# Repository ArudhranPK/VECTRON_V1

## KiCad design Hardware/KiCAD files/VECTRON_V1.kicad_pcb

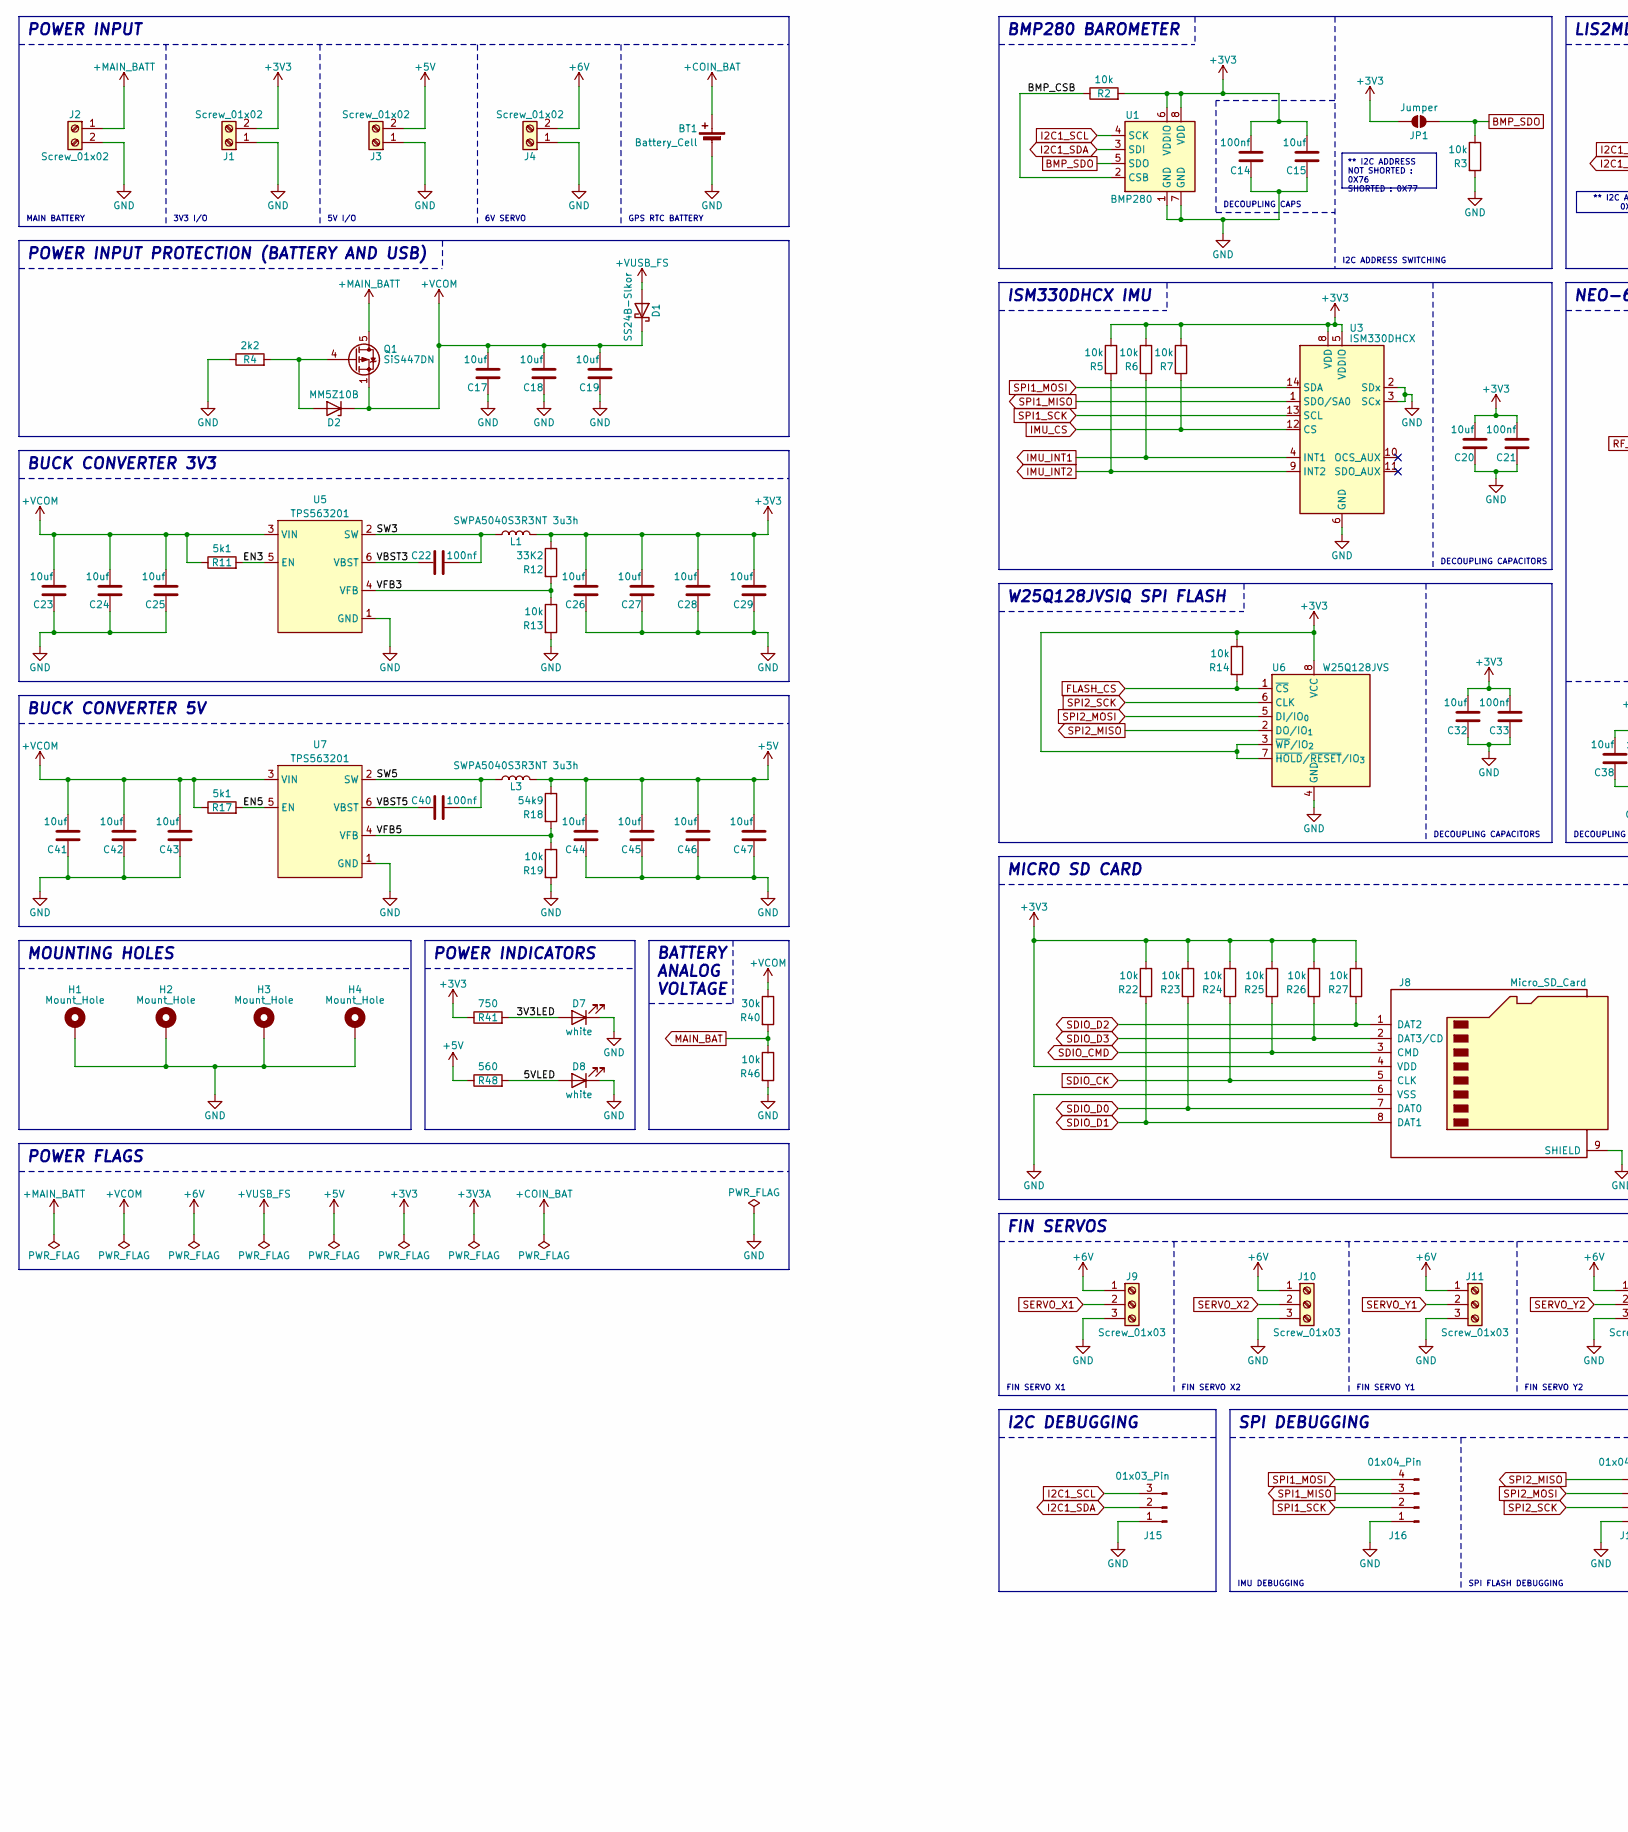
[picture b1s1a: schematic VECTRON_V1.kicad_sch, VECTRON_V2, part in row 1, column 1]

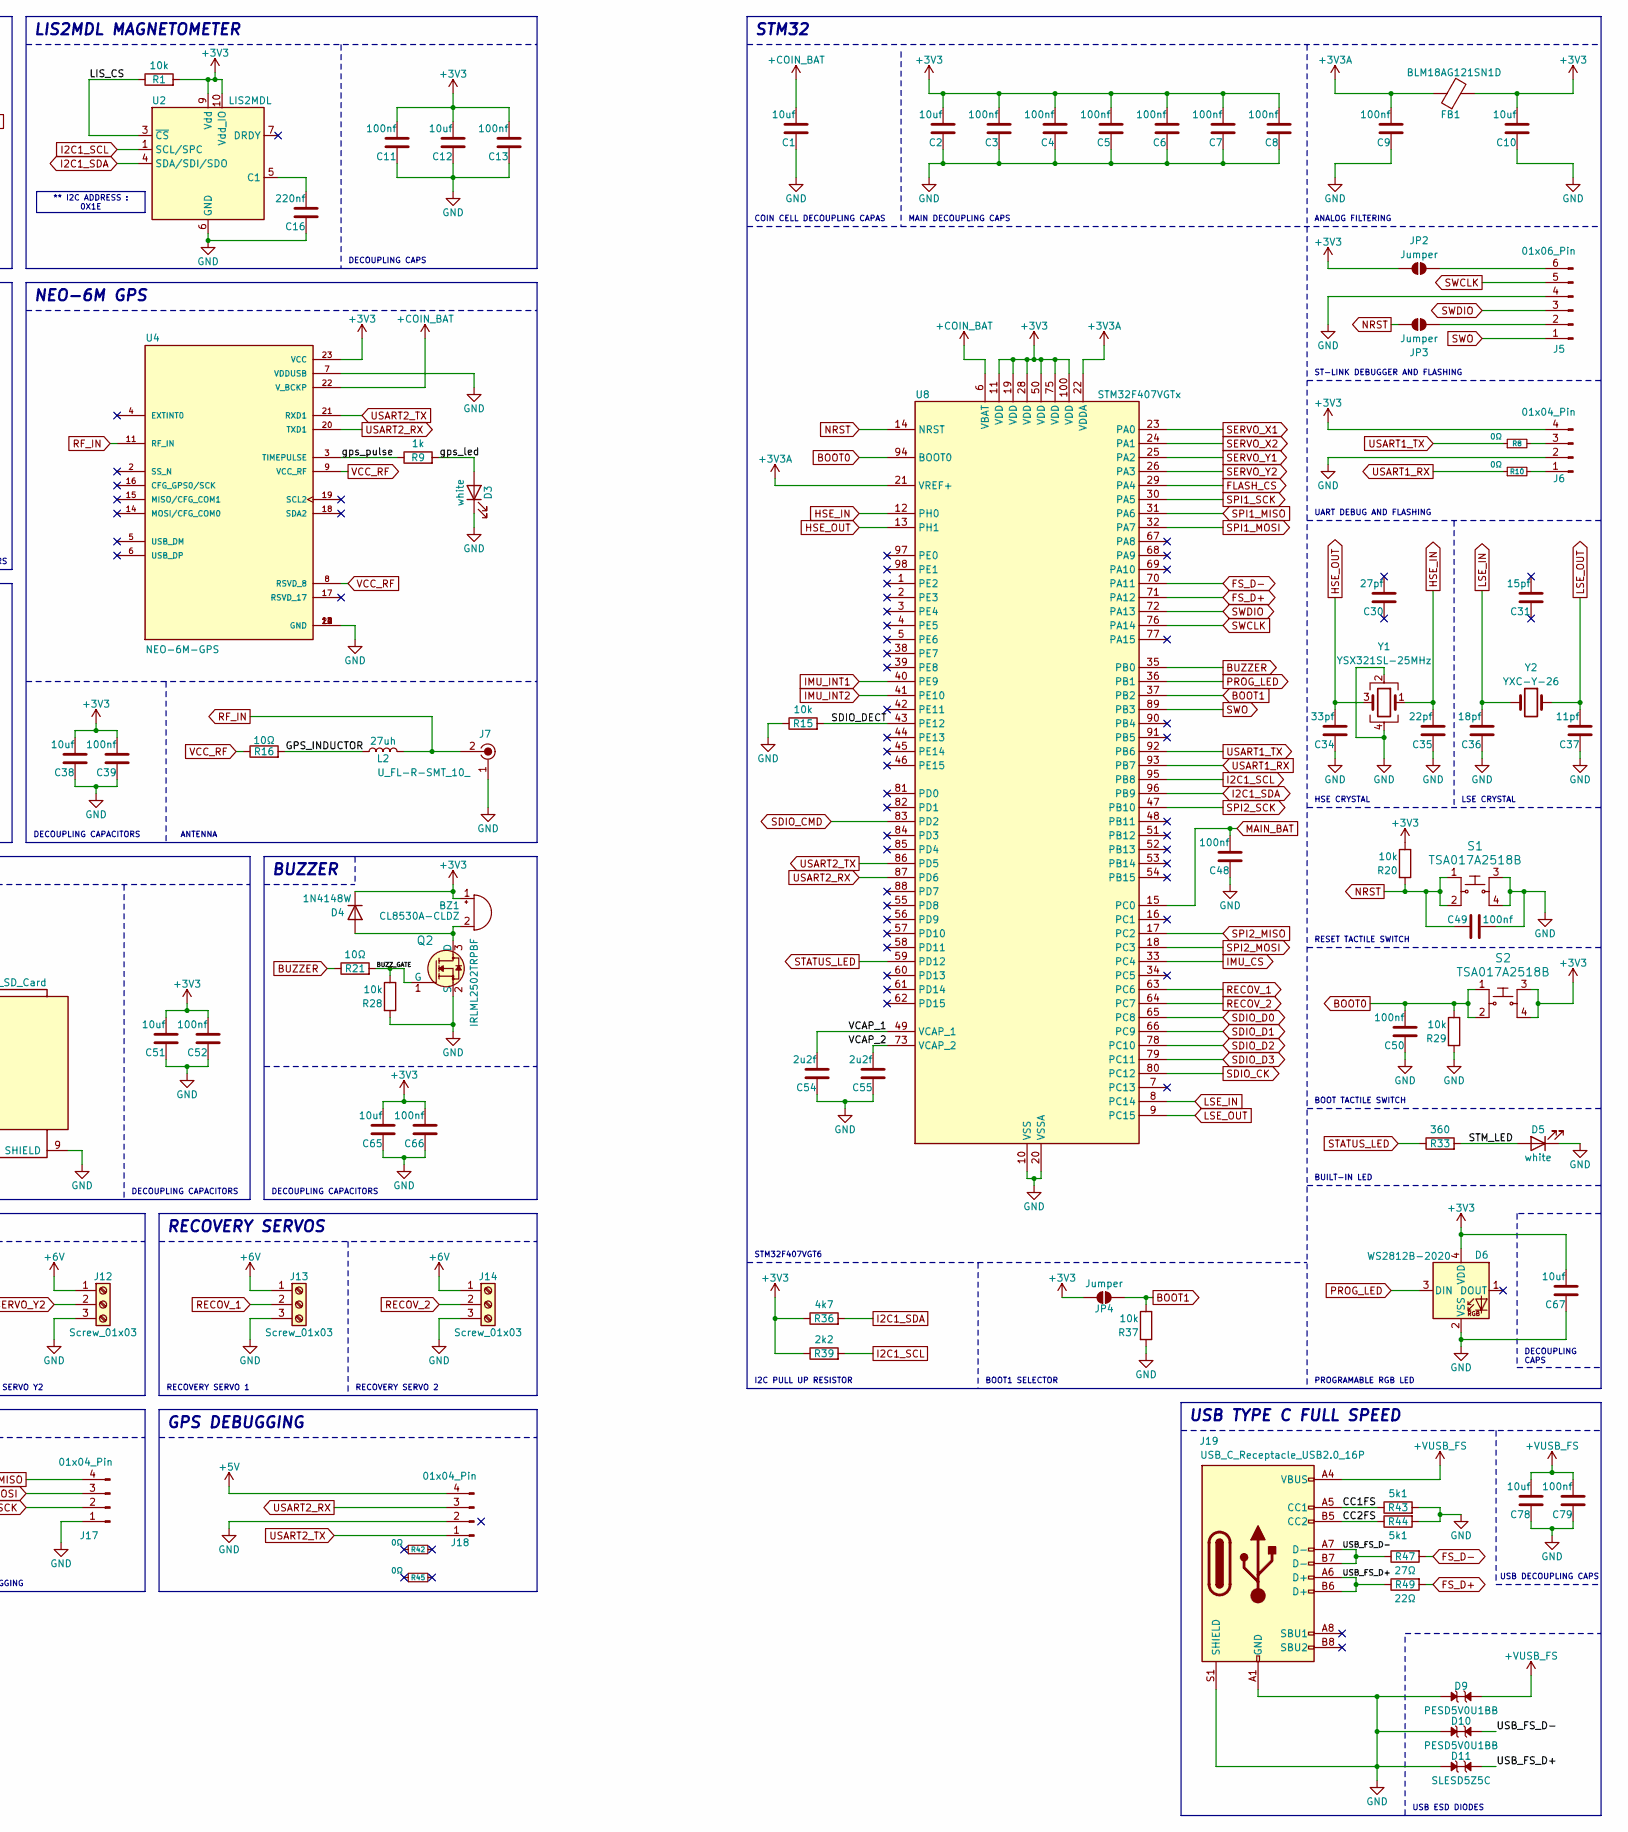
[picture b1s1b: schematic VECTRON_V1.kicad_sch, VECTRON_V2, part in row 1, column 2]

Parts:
BT1: Battery_Cell; BatteryHolder_Multicomp_BC-2001_1x2032_1
BZ1: CL8530A-CLDZ; MagneticBuzzer_CUI_CMT-8504-100-SMT
C1, C2, C10, C12, C15, C17, C18, C19, C20, C23, C24, C25, C26, C27, C28, C29, C32, C38, C41, C42, C43, C44, C45, C46, C47, C51, C65, C67, C78: 10uf; C_0603_1608Metric
C3, C4, C5, C6, C7, C8, C9, C11, C13, C14, C21, C22, C33, C39, C40, C48, C49, C50, C52, C66, C79: 100nf; C_0603_1608Metric
C16: 220nf; C_0603_1608Metric
C30: 27pf; C_0402_1005Metric
C31: 15pf; C_0402_1005Metric
C34: 33pf; C_0402_1005Metric
C35: 22pf; C_0402_1005Metric
C36: 18pf; C_0402_1005Metric
C37: 11pf; C_0402_1005Metric
C54, C55: 2u2f; C_0402_1005Metric
D1: SS24B-Slkor; D_SMA
D2: MM5Z10B; D_SOD-523
D3, D5, D7, D8: white; LED_0603_1608Metric
D4: 1N4148W; D_SOD-123
D6: WS2812B-2020; LED_WS2812B-2020_PLCC4_2.0x2.0mm
D9, D10: PESD5V0U1BB; D_SOD-523
D11: SLESD5Z5C; D_SOD-523
FB1: BLM18AG121SN1D; L_0603_1608Metric
H1, H2, H3, H4: Mount_Hole; MountingHole_3.2mm_M3_Pad_Via
J1, J3: Screw_01x02; TerminalBlock_Xinya_XY308-2.54-2P_1x02_P2.54mm_Horizontal
J2, J4: Screw_01x02; TerminalBlock_RND_205-00045_1x02_P5.00mm_Horizontal
J5: 01x06_Pin; PinHeader_1x06_P2.54mm_Vertical
J6, J16, J17, J18: 01x04_Pin; PinHeader_1x04_P2.54mm_Vertical
J7: U_FL-R-SMT_10_; Coax_Conn_U.FL; MPN U.FL-R-SMT(10); Digi-Key_PN H9161CT-ND
J8: Micro_SD_Card; microSD_HC_Molex_47219-2001
J9, J10, J11, J12, J13, J14: Screw_01x03; TerminalBlock_Xinya_XY308-2.54-3P_1x03_P2.54mm_Horizontal
J15: 01x03_Pin; PinHeader_1x03_P2.54mm_Vertical
J19: USB_C_Receptacle_USB2.0_16P; USB_C_Receptacle_GCT_USB4105-xx-A_16P_TopMnt_Horizontal
JP1, JP2, JP3, JP4: Jumper; SolderJumper-2_P1.3mm_Open_RoundedPad1.0x1.5mm
L1, L3: SWPA5040S3R3NT 3u3h; L_Sunlord_SWPA5040S
L2: 27uh; L_0805_2012Metric
Q1: SiS447DN; Vishay_PowerPAK_1212-8_Single
Q2: IRLML2502TRPBF; TSOT-23; MPN IRLML2502TRPBF; Digi-Key_PN IRLML2502TRPBFCT-ND
R1, R2, R3, R5, R6, R7, R13, R14, R15, R19, R20, R22, R23, R24, R25, R26, R27, R28, R29, R37, R46: 10k; R_0603_1608Metric
R4, R39: 2k2; R_0603_1608Metric
R8, R10, R42, R45: 0Ω; R_0603_1608Metric
R9: 1k; R_0603_1608Metric
R11, R17, R43, R44: 5k1; R_0603_1608Metric
R12: 33K2; R_0603_1608Metric
R16: 10Ω; R_0805_2012Metric
R18: 54k9; R_0603_1608Metric
R21: 10Ω; R_0603_1608Metric
R33: 360; R_0603_1608Metric
R36: 4k7; R_0603_1608Metric
R40: 30k; R_0603_1608Metric
R41: 750; R_0603_1608Metric
R47: 27Ω; R_0603_1608Metric
R48: 560; R_0603_1608Metric
R49: 22Ω; R_0603_1608Metric
S1, S2: TSA017A2518B; MPN B3F-1000; Digi-Key_PN SW400-ND
U1: BMP280; Bosch_LGA-8_2x2.5mm_P0.65mm_ClockwisePinNumbering
U2: LIS2MDL; LGA-12_2x2mm_P0.5mm
U3: ISM330DHCX; LGA-14_3x2.5mm_P0.5mm_LayoutBorder3x4y
U4: NEO-6M-GPS; XCVR_NEO-6M-GPS; PARTREV R15
U5, U7: TPS563201; SOT-23-6
U6: W25Q128JVS; SOIC-8_5.3x5.3mm_P1.27mm
U8: STM32F407VGTx; LQFP-100_14x14mm_P0.5mm
Y1: YSX321SL-25MHz; Crystal_SMD_3225-4Pin_3.2x2.5mm
Y2: YXC-Y-26; Crystal_DS26_D2.0mm_L6.0mm_Horizontal

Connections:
+3V3: BZ1.1 (+), C2.2, C3.2, C4.2, C5.2, C6.2, C7.2, C8.2, C10.2, C11.2, C12.2, C13.2, C14.2, C15.2, C20.2, C21.2, C26.2, C27.2, C28.2, C29.2, C32.2, C33.2, C38.2, C39.2, C51.2, C52.2, C65.2, C66.2, C67.2, D4.1 (K), D6.4 (VDD), FB1.2, J1.2, J6.4, J8.4 (VDD), JP1.2 (B), JP2.1 (A), JP4.2 (B), L1.2, R1.2, R2.2, R5.1, R6.1, R7.1, R12.1, R14.1, R20.1, R22.1, R23.1, R24.1, R25.1, R26.1, R27.1, R36.1, R39.1, R41.1, S2.3, S2.4, U1.6 (VDDIO), U1.8 (VDD), U2.9 (Vdd), U2.10 (Vdd_IO), U3.5 (VDDIO), U3.8 (VDD), U4.23 (VCC), U6.3 (~WP/IO_{2}), U6.7 (~HOLD/~RESET/IO_{3}), U6.8 (VCC), U8.11 (VDD), U8.19 (VDD), U8.28 (VDD), U8.50 (VDD), U8.75 (VDD), U8.100 (VDD)
+3V3A: C9.2, FB1.1, U8.21 (VREF+), U8.22 (VDDA)
+5V: C44.2, C45.2, C46.2, C47.2, J3.2, J18.4, L3.2, R18.1, R48.1
+6V: J4.2, J9.1, J10.1, J11.1, J12.1, J13.1, J14.1
+COIN_BAT: BT1.1 (+), C1.2, U4.22 (V_BCKP), U8.6 (VBAT)
+MAIN_BATT: J2.1, Q1.5 (D)
+VCOM: C17.2, C18.2, C19.2, C23.2, C24.2, C25.2, C41.2, C42.2, C43.2, D1.1 (K), D2.1 (K), Q1.1 (S), Q1.2 (S), Q1.3 (S), R11.1, R17.1, R40.1, U5.3 (VIN), U7.3 (VIN)
+VUSB_FS: C78.2, C79.2, D1.2 (A), D9.2, J19.A4 (VBUS), J19.A9 (VBUS), J19.B4 (VBUS), J19.B9 (VBUS)
/3V3LED: D7.2 (A), R41.2
/5VLED: D8.2 (A), R48.2
/BMP_CSB: R2.1, U1.2 (CSB)
/BUZZ_GATE: Q2.1 (G), R21.2, R28.1
/CC1FS: J19.A5 (CC1), R43.1
/CC2FS: J19.B5 (CC2), R44.1
/EN3: R11.2, U5.5 (EN)
/EN5: R17.2, U7.5 (EN)
/GPS_INDUCTOR: L2.1, R16.2
/LIS_CS: R1.1, U2.3 (~CS)
/SDIO_DECT: R15.2, U8.43 (PE12)
/STM_LED: D5.2 (A), R33.2
/SW3: C22.2, L1.1, U5.2 (SW)
/SW5: C40.2, L3.1, U7.2 (SW)
/USB_FS_D+: D11.2, J19.A6 (D+), J19.B6 (D+), R49.1
/USB_FS_D-: D10.2, J19.A7 (D-), J19.B7 (D-), R47.1
/VBST3: C22.1, U5.6 (VBST)
/VBST5: C40.1, U7.6 (VBST)
/VCAP_1: C54.2, U8.49 (VCAP_1)
/VCAP_2: C55.2, U8.73 (VCAP_2)
/VFB3: R12.2, R13.1, U5.4 (VFB)
/VFB5: R18.2, R19.1, U7.4 (VFB)
/gps_led: D3.2 (A), R9.2
/gps_pulse: R9.1, U4.3 (TIMEPULSE)
BMP_SDO: JP1.1 (A), R3.1, U1.5 (SDO)
BOOT0: C50.2, R29.1, S2.1, S2.2, U8.94 (BOOT0)
BOOT1: JP4.1 (A), R37.1, U8.37 (PB2)
BUZZER: R21.1, U8.35 (PB0)
FLASH_CS: R14.2, U6.1 (~CS), U8.29 (PA4)
FS_D+: R49.2, U8.71 (PA12)
FS_D-: R47.2, U8.70 (PA11)
GND: BT1.2 (-), C1.1, C2.1, C3.1, C4.1, C5.1, C6.1, C7.1, C8.1, C9.1, C10.1, C11.1, C12.1, C13.1, C14.1, C15.1, C16.1, C17.1, C18.1, C19.1, C20.1, C21.1, C23.1, C24.1, C25.1, C26.1, C27.1, C28.1, C29.1, C32.1, C33.1, C34.1, C35.1, C36.1, C37.1, C38.1, C39.1, C41.1, C42.1, C43.1, C44.1, C45.1, C46.1, C47.1, C48.1, C49.2, C50.1, C51.1, C52.1, C54.1, C55.1, C65.1, C66.1, C67.1, C78.1, C79.1, D3.1 (K), D5.1 (K), D6.2 (VSS), D7.1 (K), D8.1 (K), D9.1, D10.1, D11.1, H1.1, H2.1, H3.1, H4.1, J1.1, J2.2, J3.1, J4.1, J5.4, J6.2, J7.1, J8.6 (VSS), J8.9 (SHIELD), J9.3, J10.3, J11.3, J12.3, J13.3, J14.3, J15.1, J16.1, J17.1, J18.2, J19.A1 (GND), J19.A12 (GND), J19.B1 (GND), J19.B12 (GND), J19.S1 (SHIELD), Q2.2 (S), R3.2, R4.1, R13.2, R15.1, R19.2, R28.2, R29.2, R37.2, R43.2, R44.2, R46.2, S1.3, S1.4, U1.1 (GND), U1.7 (GND), U2.6 (GND), U2.8 (GND), U3.2 (SDx), U3.3 (SCx), U3.6 (GND), U3.7 (GND), U4.7 (VDDUSB), U4.10 (GND), U4.12 (GND), U4.13 (GND), U4.24 (GND), U5.1 (GND), U6.4 (GND), U7.1 (GND), U8.10 (VSS), U8.20 (VSSA), U8.27 (VSS), U8.74 (VSS), U8.99 (VSS), Y1.2, Y1.4
HSE_IN: C35.2, U8.12 (PH0), Y1.1
HSE_OUT: C34.2, U8.13 (PH1), Y1.3
I2C1_SCL: J15.3, R39.2, U1.4 (SCK), U2.1 (SCL/SPC), U8.95 (PB8)
I2C1_SDA: J15.2, R36.2, U1.3 (SDI), U2.4 (SDA/SDI/SDO), U8.96 (PB9)
IMU_CS: R7.2, U3.12 (CS), U8.33 (PC4)
IMU_INT1: R6.2, U3.4 (INT1), U8.40 (PE9)
IMU_INT2: R5.2, U3.9 (INT2), U8.41 (PE10)
LSE_IN: C36.2, U8.8 (PC14), Y2.2
LSE_OUT: C37.2, U8.9 (PC15), Y2.1
MAIN_BAT: C48.2, R40.2, R46.1, U8.15 (PC0)
NRST: C49.1, JP3.1 (A), R20.2, S1.1, S1.2, U8.14 (NRST)
unnamed: BZ1.2 (-), D4.2 (A), Q2.3 (D)
unnamed: D2.2 (A), Q1.4 (G), R4.2
unnamed: J5.2, JP3.2 (B)
unnamed: J5.6, JP2.2 (B)
unnamed: J6.1, R10.2
unnamed: J6.3, R8.2
unnamed: C16.2, U2.5 (C1)
PROG_LED: D6.3 (DIN), U8.36 (PB1)
RECOV_1: J13.2, U8.63 (PC6)
RECOV_2: J14.2, U8.64 (PC7)
RF_IN: J7.2, L2.2, U4.11 (RF_IN)
SDIO_CK: J8.5 (CLK), R24.2, U8.80 (PC12)
SDIO_CMD: J8.3 (CMD), R25.2, U8.83 (PD2)
SDIO_D0: J8.7 (DAT0), R23.2, U8.65 (PC8)
SDIO_D1: J8.8 (DAT1), R22.2, U8.66 (PC9)
SDIO_D2: J8.1 (DAT2), R27.2, U8.78 (PC10)
SDIO_D3: J8.2 (DAT3/CD), R26.2, U8.79 (PC11)
SERVO_X1: J9.2, U8.23 (PA0)
SERVO_X2: J10.2, U8.24 (PA1)
SERVO_Y1: J11.2, U8.25 (PA2)
SERVO_Y2: J12.2, U8.26 (PA3)
SPI1_MISO: J16.3, U3.1 (SDO/SA0), U8.31 (PA6)
SPI1_MOSI: J16.4, U3.14 (SDA), U8.32 (PA7)
SPI1_SCK: J16.2, U3.13 (SCL), U8.30 (PA5)
SPI2_MISO: J17.4, U6.2 (DO/IO_{1}), U8.17 (PC2)
SPI2_MOSI: J17.3, U6.5 (DI/IO_{0}), U8.18 (PC3)
SPI2_SCK: J17.2, U6.6 (CLK), U8.47 (PB10)
STATUS_LED: R33.1, U8.59 (PD12)
SWCLK: J5.5, U8.76 (PA14)
SWDIO: J5.3, U8.72 (PA13)
SWO: J5.1, U8.89 (PB3)
USART1_RX: R10.1, U8.93 (PB7)
USART1_TX: R8.1, U8.92 (PB6)
USART2_RX: J18.3, U4.20 (TXD1), U8.87 (PD6)
USART2_TX: J18.1, U4.21 (RXD1), U8.86 (PD5)
VCC_RF: R16.1, U4.8 (RSVD_8), U4.9 (VCC_RF)

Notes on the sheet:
BUCK CONVERTER 3V3
STM32F407VGT6
DECOUPLING CAPS
LIS2MDL MAGNETOMETER
BOOT TACTILE SWITCH
UART DEBUG AND FLASHING
FIN SERVO X2
DECOUPLING CAPACITORS
NEO-6M GPS
POWER INDICATORS
BOOT1 SELECTOR
MICRO SD CARD
SPI FLASH DEBUGGING
DECOUPLING CAPS
STM32
I2C ADDRESS SWITCHING
RECOVERY SERVO 2
ST-LINK DEBUGGER AND FLASHING
USB TYPE C FULL SPEED
GPS RTC BATTERY
6V SERVO
RECOVERY SERVO 1
FIN SERVO Y2
BUCK CONVERTER 5V
POWER INPUT
FIN SERVO X1
FIN SERVO Y1
ANALOG FILTERING
LSE CRYSTAL
MOUNTING HOLES
BATTERY ANALOG VOLTAGE
W25Q128JVSIQ SPI FLASH
SPI DEBUGGING
RECOVERY SERVOS
MAIN BATTERY
USB DECOUPLING CAPS
ISM330DHCX IMU
3V3 I/O
5V I/O
COIN CELL DECOUPLING CAPAS

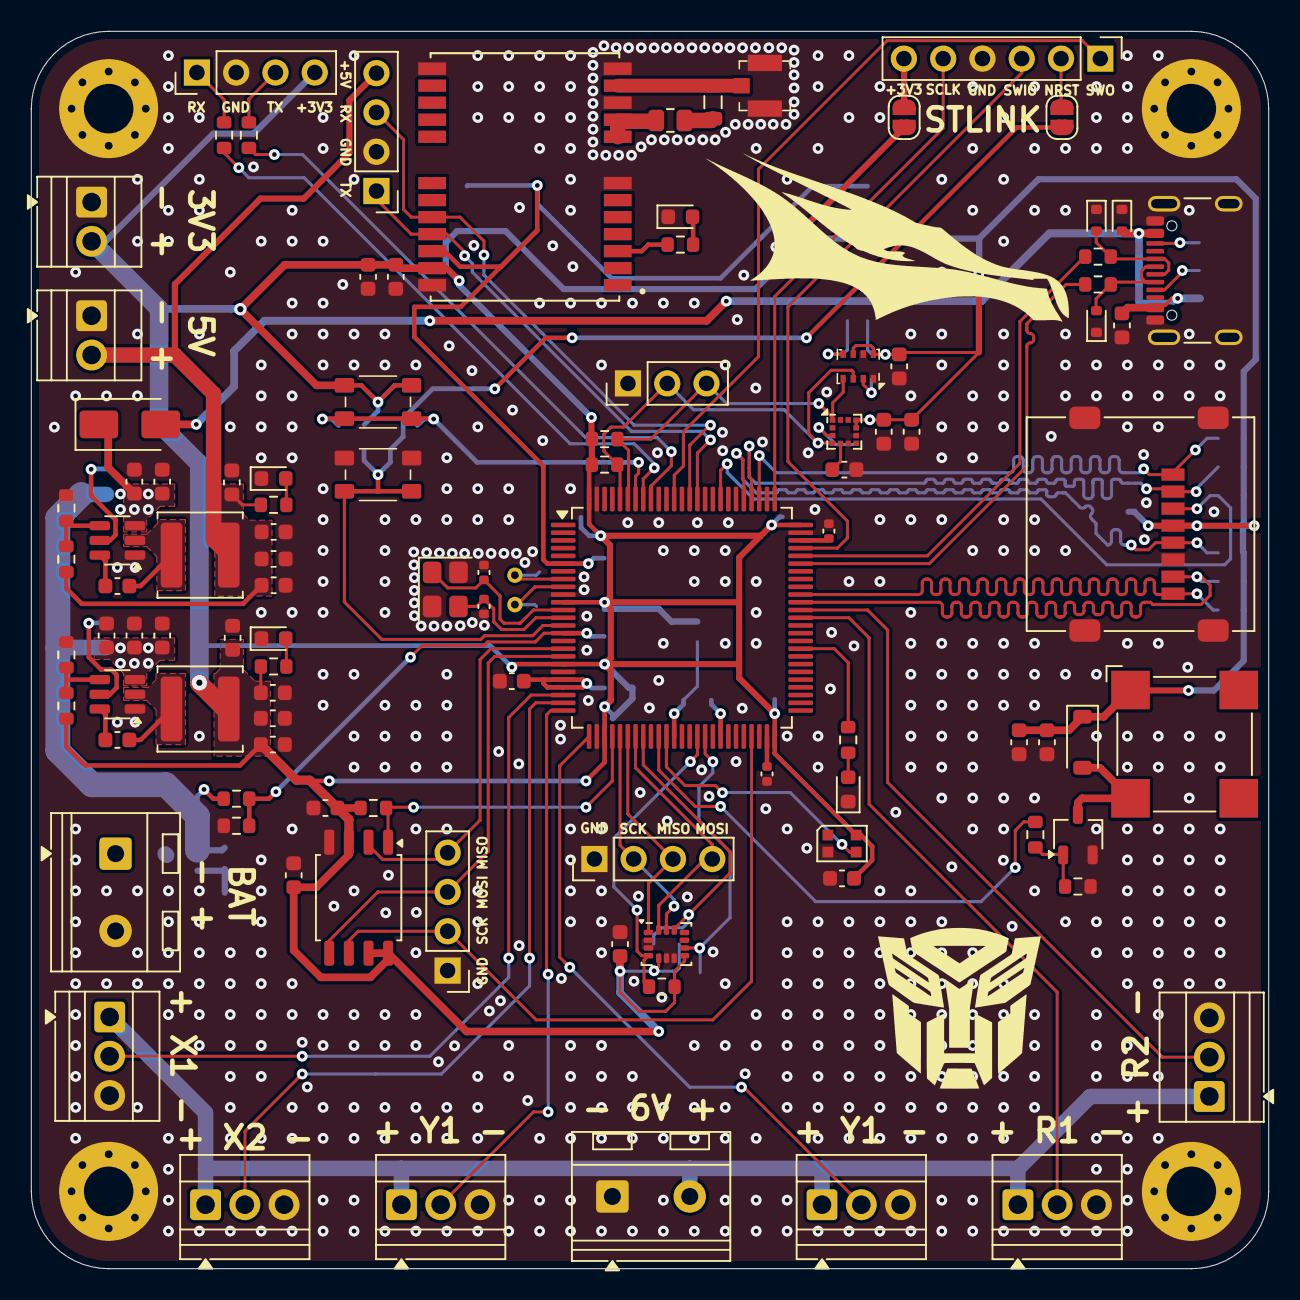
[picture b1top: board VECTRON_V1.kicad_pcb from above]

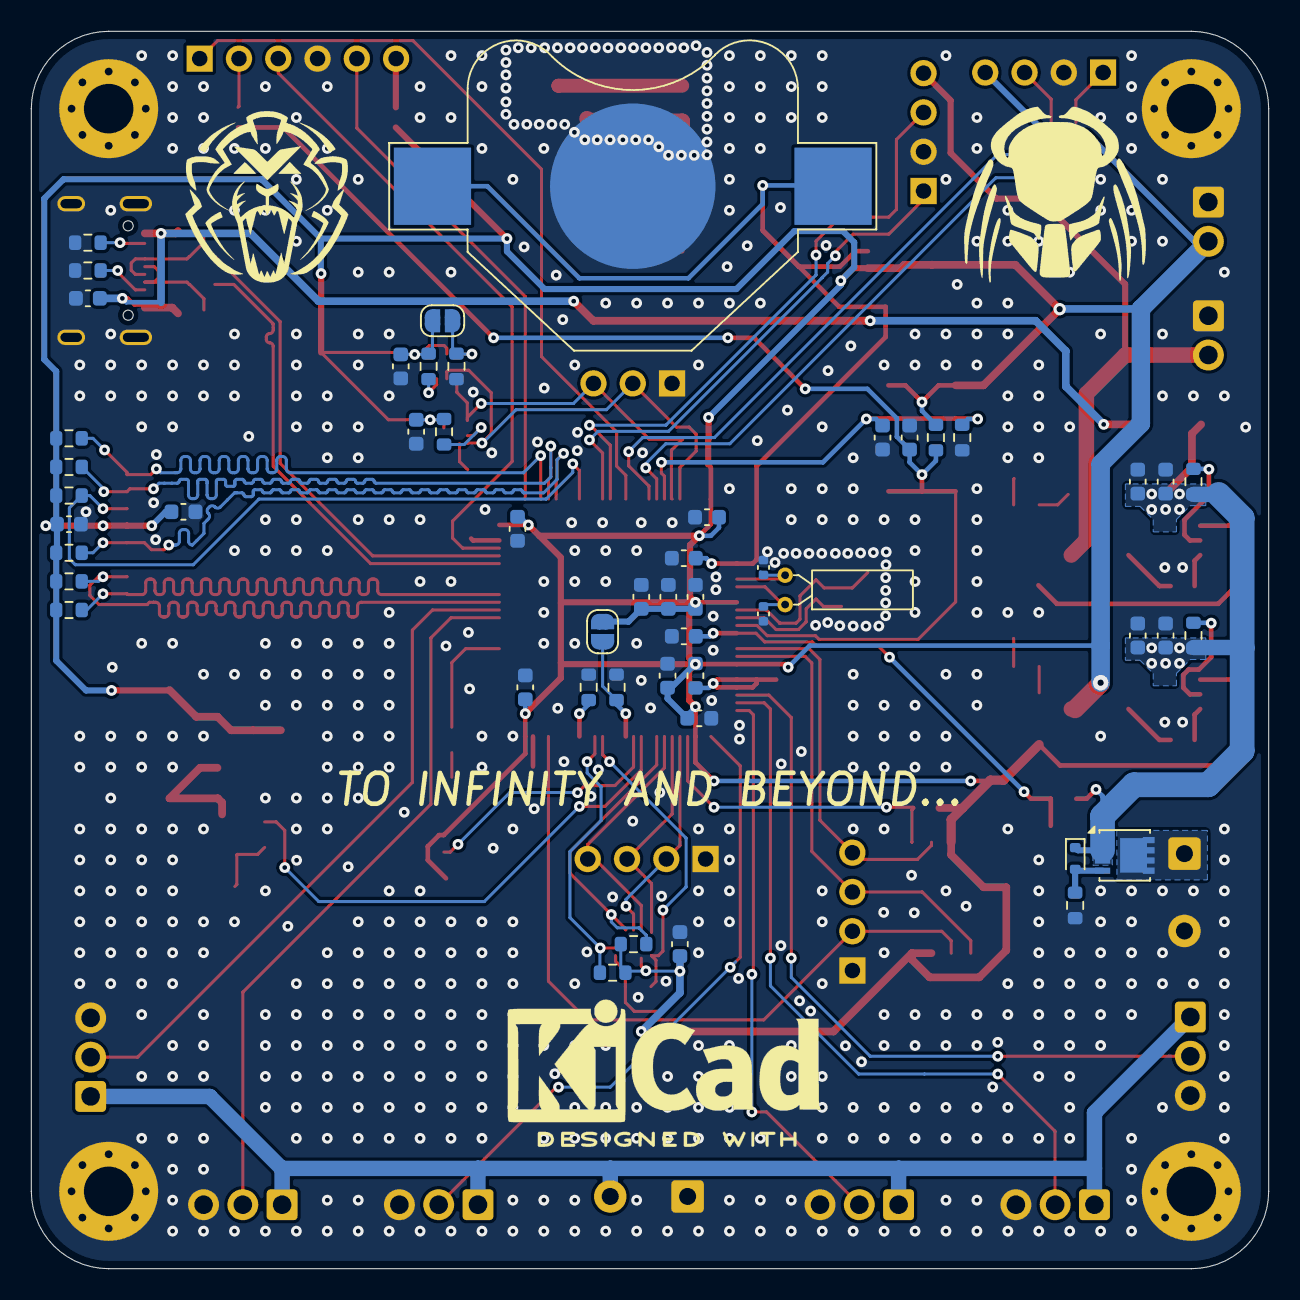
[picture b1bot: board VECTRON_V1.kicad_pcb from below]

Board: 2 copper layers, 80.0 x 80.0 mm, 156 parts (51 on the bottom side), 87 nets.

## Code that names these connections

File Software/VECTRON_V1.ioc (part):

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Mcu.Name=STM32F407V(E-G)Tx
Mcu.Package=LQFP100
Mcu.UserName=STM32F407VGTx
PA0-WKUP.GPIOParameters=GPIO_Speed
PA0-WKUP.GPIO_Speed=GPIO_SPEED_FREQ_LOW
PA0-WKUP.Signal=S_TIM2_CH1_ETR
PA1.GPIOParameters=GPIO_Speed
PA1.GPIO_Speed=GPIO_SPEED_FREQ_LOW
PA1.Signal=S_TIM2_CH2
PA11.Mode=Device_Only
PA11.Signal=USB_OTG_FS_DM
PA12.Mode=Device_Only
PA12.Signal=USB_OTG_FS_DP
PA13.Mode=Trace_Asynchronous_SW
PA13.Signal=SYS_JTMS-SWDIO
PA14.Mode=Trace_Asynchronous_SW
PA14.Signal=SYS_JTCK-SWCLK
PA2.GPIOParameters=GPIO_Speed
PA2.GPIO_Speed=GPIO_SPEED_FREQ_LOW
PA2.Signal=S_TIM2_CH3
PA3.GPIOParameters=GPIO_Speed
PA3.GPIO_Speed=GPIO_SPEED_FREQ_LOW
PA3.Signal=S_TIM2_CH4
PA4.GPIOParameters=GPIO_Label
PA4.GPIO_Label=FLASH_CS
PA4.Signal=GPIO_Output
PA5.Mode=Full_Duplex_Master
PA5.Signal=SPI1_SCK
PA6.Mode=Full_Duplex_Master
PA6.Signal=SPI1_MISO
PA7.Mode=Full_Duplex_Master
PA7.Signal=SPI1_MOSI
PB0.Mode=Output Compare2 CH2N
PB0.Signal=TIM1_CH2N
PB1.Mode=PWM Generation3 CH3N
PB1.Signal=TIM8_CH3N
PB10.Mode=Full_Duplex_Master
PB10.Signal=SPI2_SCK
PB3.Mode=Trace_Asynchronous_SW
PB3.Signal=SYS_JTDO-SWO
PB6.Mode=Asynchronous
PB6.Signal=USART1_TX
PB7.Mode=Asynchronous
PB7.Signal=USART1_RX
PB8.Mode=I2C
PB8.Signal=I2C1_SCL
PB9.Mode=I2C
PB9.Signal=I2C1_SDA
PC0.Signal=ADCx_IN10
PC10.Mode=SD_4_bits_Wide_bus
PC10.Signal=SDIO_D2
PC11.Mode=SD_4_bits_Wide_bus
PC11.Signal=SDIO_D3
PC12.Mode=SD_4_bits_Wide_bus
PC12.Signal=SDIO_CK
PC14-OSC32_IN.Mode=LSE-External-Oscillator
PC14-OSC32_IN.Signal=RCC_OSC32_IN
PC15-OSC32_OUT.Mode=LSE-External-Oscillator
PC15-OSC32_OUT.Signal=RCC_OSC32_OUT
PC2.Mode=Full_Duplex_Master
PC2.Signal=SPI2_MISO
PC3.Mode=Full_Duplex_Master
PC3.Signal=SPI2_MOSI
PC4.GPIOParameters=GPIO_Label
PC4.GPIO_Label=IMU_CS
PC4.Signal=GPIO_Output
PC6.Signal=S_TIM3_CH1
PC7.Signal=S_TIM3_CH2
PC8.Mode=SD_4_bits_Wide_bus
PC8.Signal=SDIO_D0
PC9.Mode=SD_4_bits_Wide_bus
PC9.Signal=SDIO_D1
PD12.GPIOParameters=GPIO_Label
PD12.GPIO_Label=STATUS_LED
PD12.Signal=GPIO_Output
PD2.Mode=SD_4_bits_Wide_bus
PD2.Signal=SDIO_CMD
PD5.Mode=Asynchronous
PD5.Signal=USART2_TX
PD6.Mode=Asynchronous
PD6.Signal=USART2_RX
PE10.GPIOParameters=GPIO_Label
PE10.GPIO_Label=IMU_INT_2
PE10.Signal=GPXTI10
PE12.GPIOParameters=GPIO_Label
PE12.GPIO_Label=SDIO_DET
PE12.Signal=GPIO_Input
PE9.GPIOParameters=GPIO_PuPd,GPIO_Label,GPIO_ModeDefaultEXTI
PE9.GPIO_Label=IMU_INT_1
PE9.GPIO_ModeDefaultEXTI=GPIO_MODE_IT_FALLING
PE9.GPIO_PuPd=GPIO_NOPULL
PE9.Signal=GPXTI9
PH0-OSC_IN.Mode=HSE-External-Oscillator
PH0-OSC_IN.Signal=RCC_OSC_IN
PH1-OSC_OUT.Mode=HSE-External-Oscillator
PH1-OSC_OUT.Signal=RCC_OSC_OUT
RCC.HSE_VALUE=25000000
RCC.SYSCLKFreq_VALUE=168000000
RCC.SYSCLKSource=RCC_SYSCLKSOURCE_PLLCLK
board=custom

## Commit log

2025-08-31 Software framework
2025-08-31 planning added
2025-09-01 changed MCU
2025-09-04 added bmp and magnetometer
2025-09-07 all connections made rechecking needed
2025-09-12 finished according to me :)
2025-09-12 tiny changes
2025-11-18 final changes
2026-01-16 data logging
